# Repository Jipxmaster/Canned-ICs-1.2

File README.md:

# Canned-ICs-2
"Chips Enlatados" es un proyecto en la que intento colocar el mayor número de integrados de la serie 7400 en el menor espacio posible.

-La salida del compilador se puede copiar a la memoria interna de la computadora en la simulación Logisim
-La versión de KiCAD es 6.0

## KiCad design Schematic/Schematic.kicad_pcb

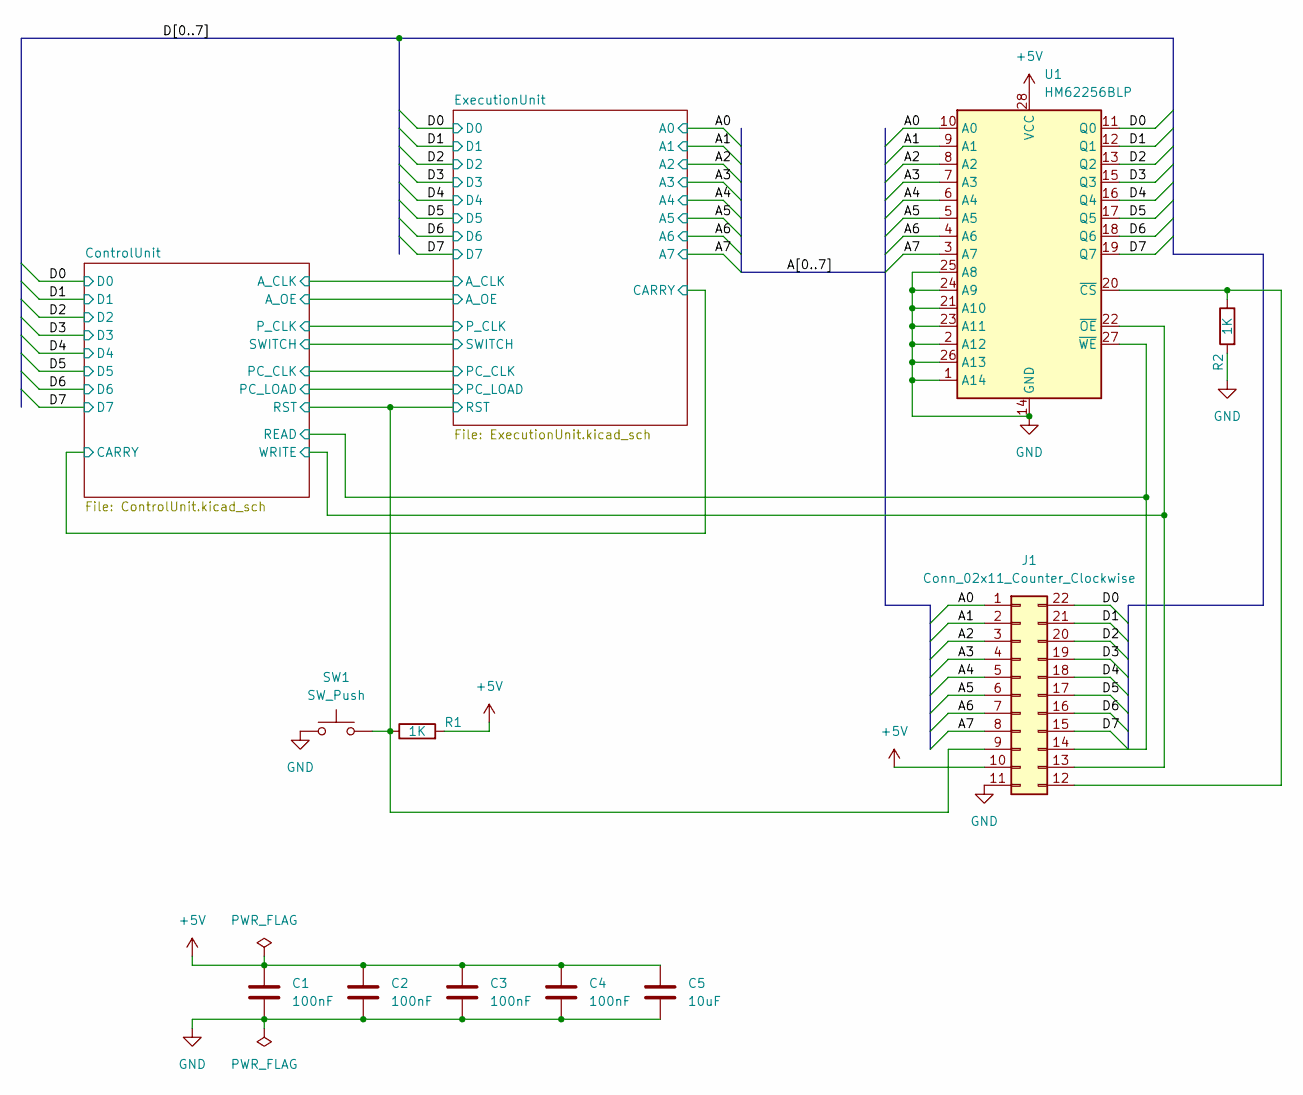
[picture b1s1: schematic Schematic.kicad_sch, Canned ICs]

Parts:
C1, C2, C3, C4: 100nF; C_Disc_D3.0mm_W1.6mm_P2.50mm
C5: 10uF; CP_Radial_D5.0mm_P2.00mm
J1: Conn_02x11_Counter_Clockwise; PinSocket_2x11_P2.54mm_Vertical
R1, R2: 1K; R_Axial_DIN0204_L3.6mm_D1.6mm_P2.54mm_Vertical
SW1: SW_Push; SW_PUSH_6mm
U1: HM62256BLP; DIP-28_W15.24mm

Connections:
+5V: C1.1, C2.1, C3.1, C4.1, C5.1, J1.10, R1.2, U1.28 (VCC); also elsewhere on the board
/A0: J1.1, U1.10 (A0); also elsewhere on the board
/A1: J1.2, U1.9 (A1); also elsewhere on the board
/A2: J1.3, U1.8 (A2); also elsewhere on the board
/A3: J1.4, U1.7 (A3); also elsewhere on the board
/A4: J1.5, U1.6 (A4); also elsewhere on the board
/A5: J1.6, U1.5 (A5); also elsewhere on the board
/A6: J1.7, U1.4 (A6); also elsewhere on the board
/A7: J1.8, U1.3 (A7); also elsewhere on the board
/ControlUnit/READ: J1.14, U1.27 (~WE); also elsewhere on the board
/ControlUnit/RST: J1.9, R1.1, SW1.2; also elsewhere on the board
/ControlUnit/WRITE: J1.13, U1.22 (~OE); also elsewhere on the board
/D0: J1.22, U1.11 (Q0); also elsewhere on the board
/D1: J1.21, U1.12 (Q1); also elsewhere on the board
/D2: J1.20, U1.13 (Q2); also elsewhere on the board
/D3: J1.19, U1.15 (Q3); also elsewhere on the board
/D4: J1.18, U1.16 (Q4); also elsewhere on the board
/D5: J1.17, U1.17 (Q5); also elsewhere on the board
/D6: J1.16, U1.18 (Q6); also elsewhere on the board
/D7: J1.15, U1.19 (Q7); also elsewhere on the board
GND: C1.2, C2.2, C3.2, C4.2, C5.2, J1.11, R2.2, SW1.1, U1.1 (A14), U1.2 (A12), U1.14 (GND), U1.21 (A10), U1.23 (A11), U1.24 (A9), U1.25 (A8), U1.26 (A13); also elsewhere on the board
unnamed: J1.12, R2.1, U1.20 (~CS)

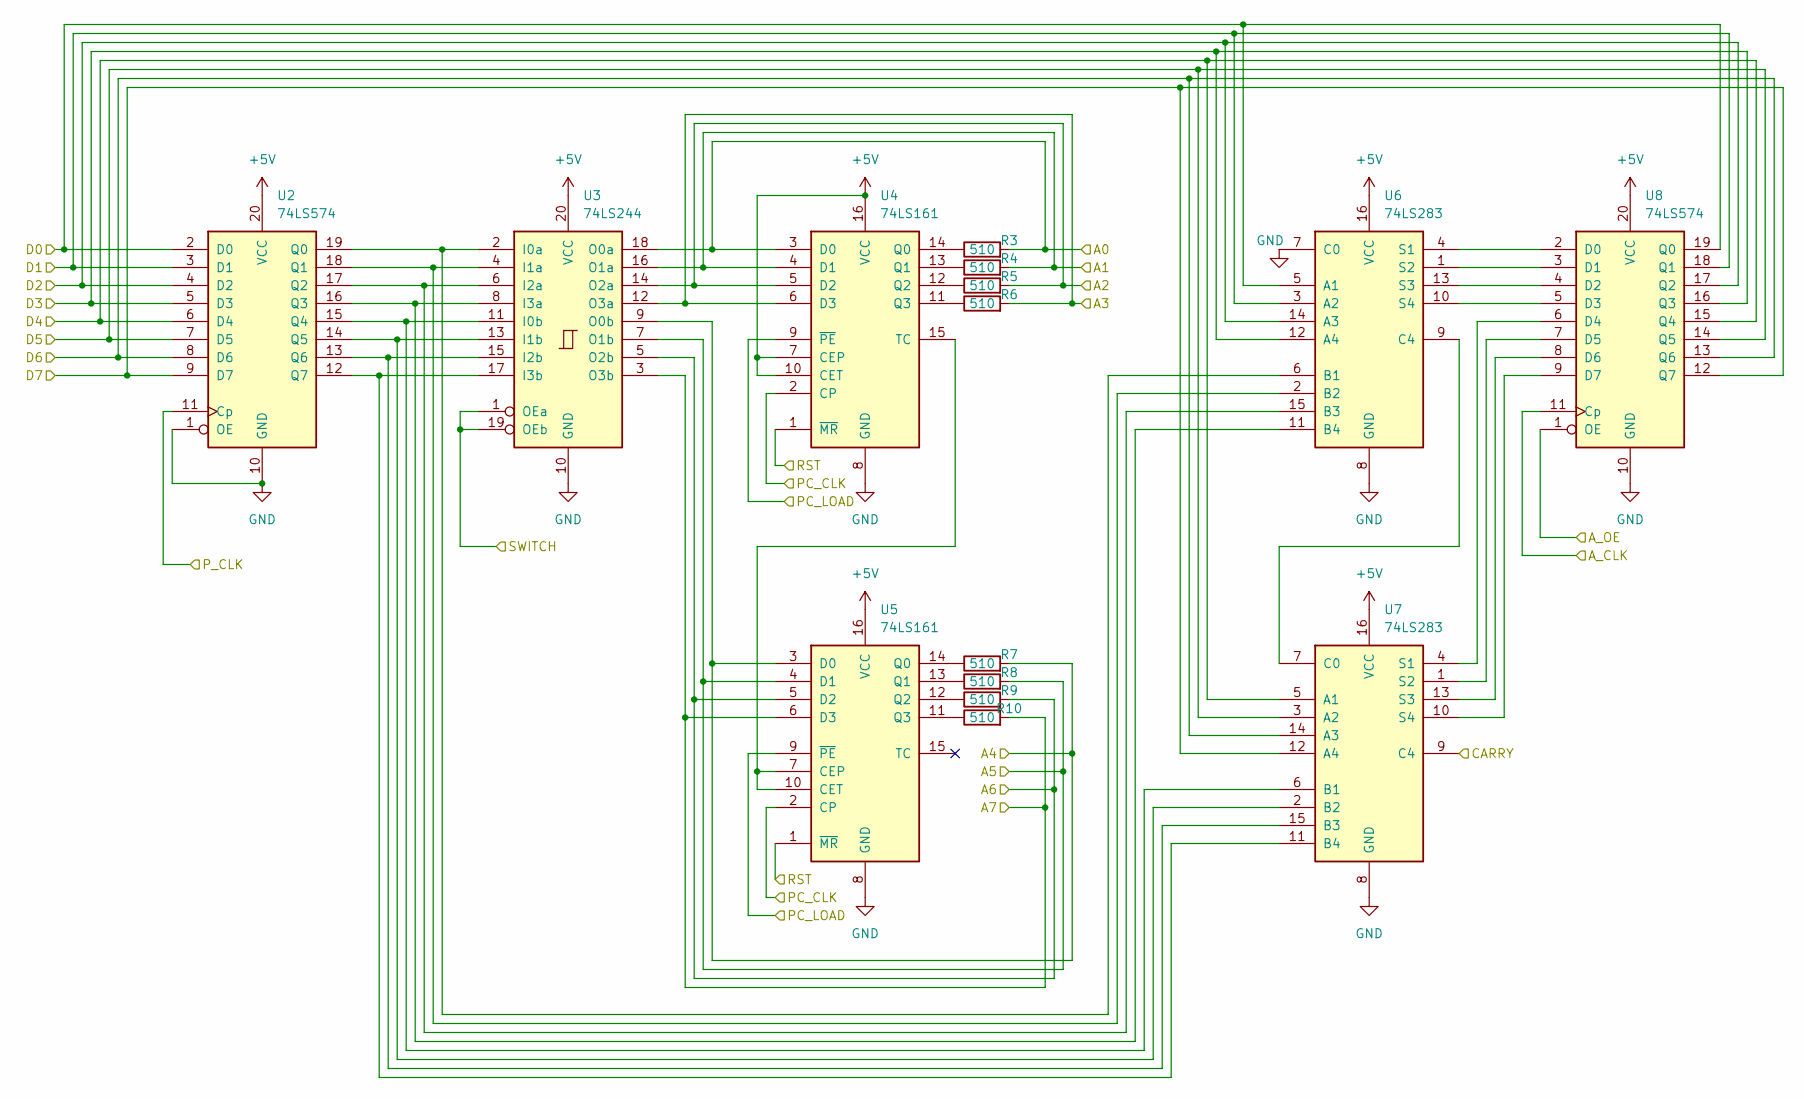
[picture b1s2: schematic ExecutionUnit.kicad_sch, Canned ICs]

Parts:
R3, R4, R5, R6, R7, R8, R9, R10: 510; R_Axial_DIN0204_L3.6mm_D1.6mm_P2.54mm_Vertical
U2, U8: 74LS574; DIP-20_W7.62mm
U3: 74LS244; DIP-20_W7.62mm
U4, U5: 74LS161; DIP-16_W7.62mm
U6, U7: 74LS283; DIP-16_W7.62mm

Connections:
+5V: U2.20 (VCC), U3.20 (VCC), U4.7 (CEP), U4.10 (CET), U4.16 (VCC), U5.16 (VCC), U6.16 (VCC), U7.16 (VCC), U8.20 (VCC); also elsewhere on the board
/A0: R3.2, U3.18 (O0a), U4.3 (D0); also elsewhere on the board
/A1: R4.2, U3.16 (O1a), U4.4 (D1); also elsewhere on the board
/A2: R5.2, U3.14 (O2a), U4.5 (D2); also elsewhere on the board
/A3: R6.2, U3.12 (O3a), U4.6 (D3); also elsewhere on the board
/A4: R7.2, U3.9 (O0b), U5.3 (D0); also elsewhere on the board
/A5: R8.2, U3.7 (O1b), U5.4 (D1); also elsewhere on the board
/A6: R9.2, U3.5 (O2b), U5.5 (D2); also elsewhere on the board
/A7: R10.2, U3.3 (O3b), U5.6 (D3); also elsewhere on the board
/ControlUnit/A_CLK: U8.11 (Cp); also elsewhere on the board
/ControlUnit/A_OE: U8.1 (OE); also elsewhere on the board
/ControlUnit/CARRY: U7.9 (C4); also elsewhere on the board
/ControlUnit/PC_CLK: U4.2 (CP), U5.2 (CP); also elsewhere on the board
/ControlUnit/PC_LOAD: U4.9 (~PE), U5.9 (~PE); also elsewhere on the board
/ControlUnit/P_CLK: U2.11 (Cp); also elsewhere on the board
/ControlUnit/RST: U4.1 (~MR), U5.1 (~MR); also elsewhere on the board
/ControlUnit/SWITCH: U3.1 (OEa), U3.19 (OEb); also elsewhere on the board
/D0: U2.2 (D0), U6.5 (A1), U8.19 (Q0); also elsewhere on the board
/D1: U2.3 (D1), U6.3 (A2), U8.18 (Q1); also elsewhere on the board
/D2: U2.4 (D2), U6.14 (A3), U8.17 (Q2); also elsewhere on the board
/D3: U2.5 (D3), U6.12 (A4), U8.16 (Q3); also elsewhere on the board
/D4: U2.6 (D4), U7.5 (A1), U8.15 (Q4); also elsewhere on the board
/D5: U2.7 (D5), U7.3 (A2), U8.14 (Q5); also elsewhere on the board
/D6: U2.8 (D6), U7.14 (A3), U8.13 (Q6); also elsewhere on the board
/D7: U2.9 (D7), U7.12 (A4), U8.12 (Q7); also elsewhere on the board
GND: U2.1 (OE), U2.10 (GND), U3.10 (GND), U4.8 (GND), U5.8 (GND), U6.7 (C0), U6.8 (GND), U7.8 (GND), U8.10 (GND); also elsewhere on the board
unnamed: R3.1, U4.14 (Q0)
unnamed: R4.1, U4.13 (Q1)
unnamed: R5.1, U4.12 (Q2)
unnamed: R6.1, U4.11 (Q3)
unnamed: R7.1, U5.14 (Q0)
unnamed: R8.1, U5.13 (Q1)
unnamed: R9.1, U5.12 (Q2)
unnamed: R10.1, U5.11 (Q3)
unnamed: U2.12 (Q7), U3.17 (I3b), U7.11 (B4)
unnamed: U2.13 (Q6), U3.15 (I2b), U7.15 (B3)
unnamed: U2.14 (Q5), U3.13 (I1b), U7.2 (B2)
unnamed: U2.15 (Q4), U3.11 (I0b), U7.6 (B1)
unnamed: U2.16 (Q3), U3.8 (I3a), U6.11 (B4)
unnamed: U2.17 (Q2), U3.6 (I2a), U6.15 (B3)
unnamed: U2.18 (Q1), U3.4 (I1a), U6.2 (B2)
unnamed: U2.19 (Q0), U3.2 (I0a), U6.6 (B1)
unnamed: U4.15 (TC), U5.7 (CEP), U5.10 (CET)
unnamed: U6.1 (S2), U8.3 (D1)
unnamed: U6.4 (S1), U8.2 (D0)
unnamed: U6.9 (C4), U7.7 (C0)
unnamed: U6.10 (S4), U8.5 (D3)
unnamed: U6.13 (S3), U8.4 (D2)
unnamed: U7.1 (S2), U8.7 (D5)
unnamed: U7.4 (S1), U8.6 (D4)
unnamed: U7.10 (S4), U8.9 (D7)
unnamed: U7.13 (S3), U8.8 (D6)

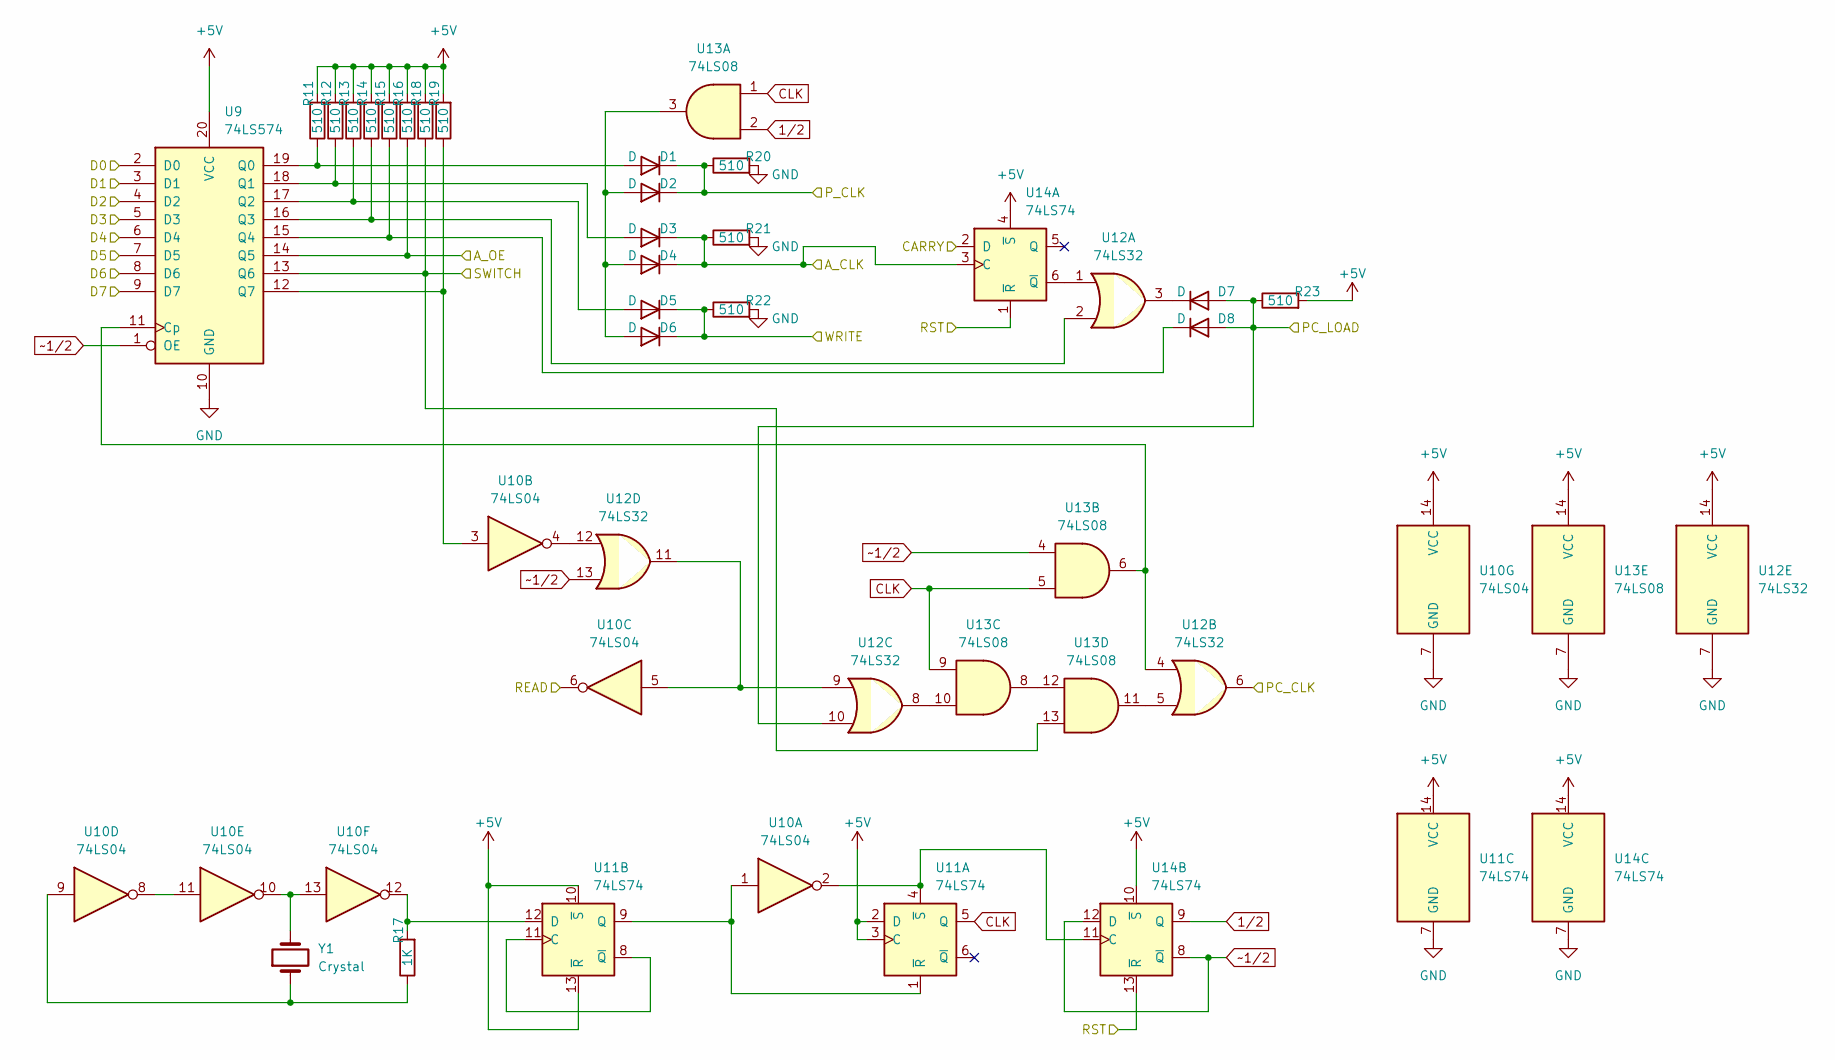
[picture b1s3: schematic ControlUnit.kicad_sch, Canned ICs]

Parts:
D1, D2, D3, D4, D5, D6, D7, D8: D; D_A-405_P2.54mm_Vertical_KathodeUp
R11, R12, R13, R14, R15, R16, R18, R19, R20, R21, R22, R23: 510; R_Axial_DIN0204_L3.6mm_D1.6mm_P2.54mm_Vertical
R17: 1K; R_Axial_DIN0204_L3.6mm_D1.6mm_P2.54mm_Vertical
U9: 74LS574; DIP-20_W7.62mm
U10: 74LS04; DIP-14_W7.62mm
U11, U14: 74LS74; DIP-14_W7.62mm
U12: 74LS32; DIP-14_W7.62mm
U13: 74LS08; DIP-14_W7.62mm
Y1: Crystal; Crystal_HC49-U_Vertical

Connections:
1/2: U13.2, U14.9 (Q)
+5V: R11.2, R12.2, R13.2, R14.2, R15.2, R16.2, R18.2, R19.2, R23.2, U9.20 (VCC), U10.14 (VCC), U11.2 (D), U11.3 (C), U11.10 (~S), U11.13 (~R), U11.14 (VCC), U12.14 (VCC), U13.14 (VCC), U14.4 (~S), U14.10 (~S), U14.14 (VCC); also elsewhere on the board
/ControlUnit/A_CLK: D3.1 (K), D4.1 (K), R21.1, U14.3 (C); also elsewhere on the board
/ControlUnit/A_OE: R16.1, U9.14 (Q5); also elsewhere on the board
/ControlUnit/CARRY: U14.2 (D); also elsewhere on the board
/ControlUnit/PC_CLK: U12.6; also elsewhere on the board
/ControlUnit/PC_LOAD: D7.2 (A), D8.2 (A), R23.1, U12.10; also elsewhere on the board
/ControlUnit/P_CLK: D1.1 (K), D2.1 (K), R20.1; also elsewhere on the board
/ControlUnit/READ: U10.6; also elsewhere on the board
/ControlUnit/RST: U14.1 (~R), U14.13 (~R); also elsewhere on the board
/ControlUnit/SWITCH: R18.1, U9.13 (Q6), U13.13; also elsewhere on the board
/ControlUnit/WRITE: D5.1 (K), D6.1 (K), R22.1; also elsewhere on the board
/D0: U9.2 (D0); also elsewhere on the board
/D1: U9.3 (D1); also elsewhere on the board
/D2: U9.4 (D2); also elsewhere on the board
/D3: U9.5 (D3); also elsewhere on the board
/D4: U9.6 (D4); also elsewhere on the board
/D5: U9.7 (D5); also elsewhere on the board
/D6: U9.8 (D6); also elsewhere on the board
/D7: U9.9 (D7); also elsewhere on the board
CLK: U11.5 (Q), U13.1, U13.5, U13.9
GND: R20.2, R21.2, R22.2, U9.10 (GND), U10.7 (GND), U11.7 (GND), U12.7 (GND), U13.7 (GND), U14.7 (GND); also elsewhere on the board
unnamed: D1.2 (A), R11.1, U9.19 (Q0)
unnamed: D2.2 (A), D4.2 (A), D6.2 (A), U13.3
unnamed: D3.2 (A), R12.1, U9.18 (Q1)
unnamed: D5.2 (A), R13.1, U9.17 (Q2)
unnamed: D7.1 (K), U12.3
unnamed: D8.1 (K), R15.1, U9.15 (Q4)
unnamed: R14.1, U9.16 (Q3), U12.2
unnamed: R17.1, U10.9, Y1.1
unnamed: R17.2, U10.12, U11.12 (D)
unnamed: R19.1, U9.12 (Q7), U10.3
unnamed: U10.1, U11.1 (~R), U11.9 (Q)
unnamed: U10.2, U11.4 (~S), U14.11 (C)
unnamed: U10.4, U12.12
unnamed: U10.5, U12.9, U12.11
unnamed: U10.10, U10.13, Y1.2
unnamed: U10.8, U10.11
unnamed: U11.8 (~Q), U11.11 (C)
unnamed: U12.1, U14.6 (~Q)
unnamed: U9.11 (Cp), U12.4, U13.6
unnamed: U12.5, U13.11
unnamed: U12.8, U13.10
unnamed: U13.8, U13.12
~1/2: U9.1 (OE), U12.13, U13.4, U14.8 (~Q), U14.12 (D)

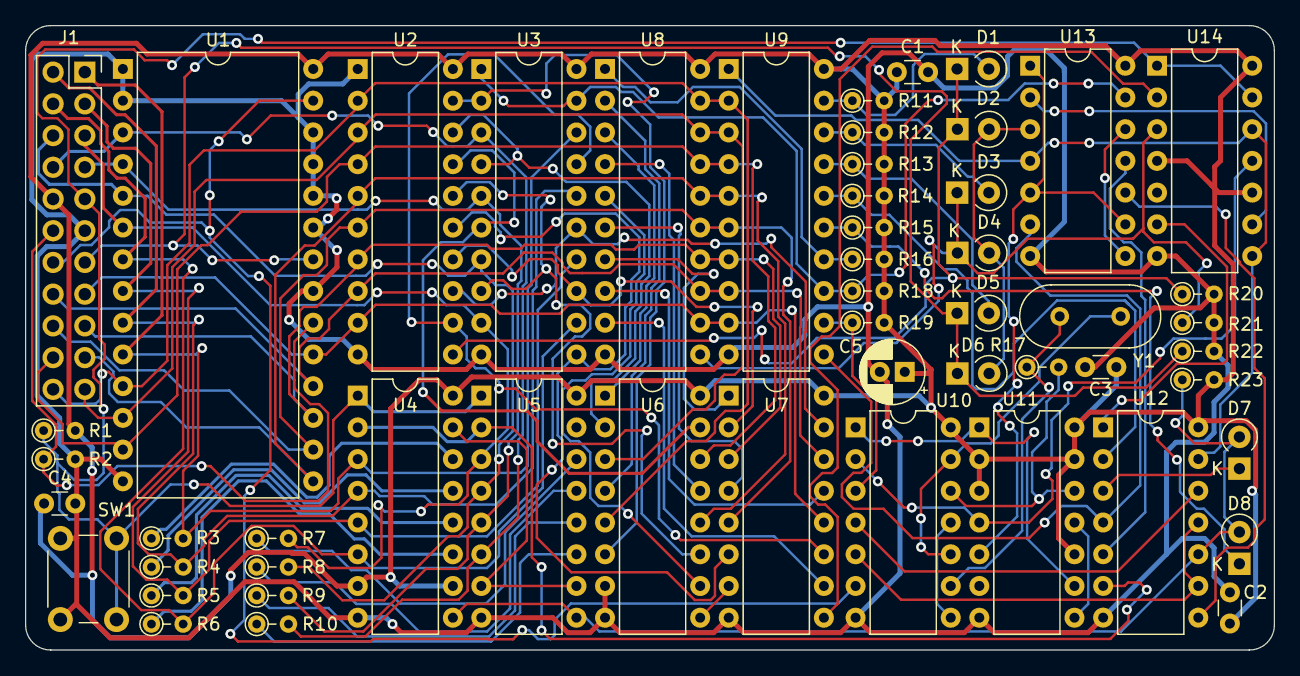
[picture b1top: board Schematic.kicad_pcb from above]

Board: 2 copper layers, 100.0 x 50.0 mm, 53 parts (0 on the bottom side), 80 nets.

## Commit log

2024-08-31 Esquemático KICAD
2024-08-31 Previsualización
2024-08-31 Simulación Logisim
